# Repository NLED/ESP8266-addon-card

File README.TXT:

THERE IS NO WARRANTY FOR THE PROGRAM, TO THE EXTENT PERMITTED BY APPLICABLE LAW. 
EXCEPT WHEN OTHERWISE STATED IN WRITING THE COPYRIGHT HOLDERS AND/OR OTHER PARTIES 
PROVIDE THE PROGRAM “AS IS” WITHOUT WARRANTY OF ANY KIND, EITHER EXPRESSED OR IMPLIED,
INCLUDING, BUT NOT LIMITED TO, THE IMPLIED WARRANTIES OF MERCHANTABILITY AND FITNESS 
FOR A PARTICULAR PURPOSE. THE ENTIRE RISK AS TO THE QUALITY AND PERFORMANCE OF THE 
PROGRAM IS WITH YOU. SHOULD THE PROGRAM PROVE DEFECTIVE, YOU ASSUME THE COST OF ALL 
NECESSARY SERVICING, REPAIR OR CORRECTION.

 Original Author: Jeffrey Nygaard
 Company: Northern Lights Electronic Design, LLC
 Date: November 17, 2017
 Contact: JNygaard@NLEDshop.com
 Copyright© 2017 by Northern Lights Electronic Design, LLC. All Rights Reserved
 
;=============          www.NLEDShop.com/addoncards           ============
;=============     www.NorthernLightsElectronicDesign.com       ============

This work is licensed under a Creative Commons Attribution 4.0 International License.

Free to use for personal or commercial use, just attribute the author if releasing changes.

================================================================================================================

Ready-made devices are available for purchase, and large batch manufacturing of any device can be requested.
Please see the webpage www.NLEDShop.com/addoncards

NLED is available for custom design and manufacturing, please contact via phone or email to discuss your project.

================================================================================================================

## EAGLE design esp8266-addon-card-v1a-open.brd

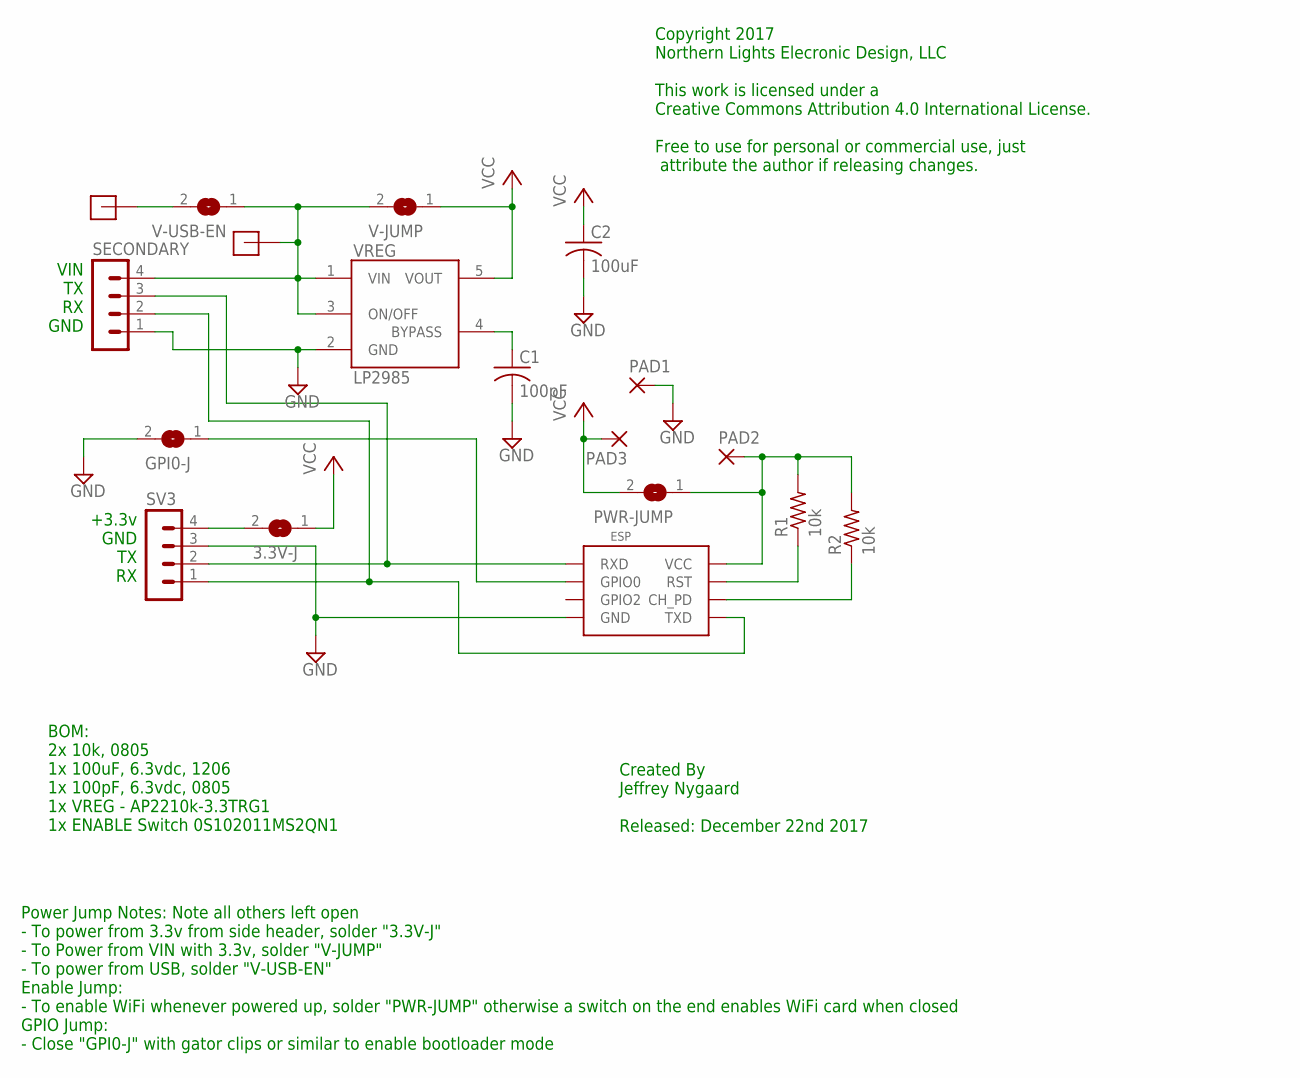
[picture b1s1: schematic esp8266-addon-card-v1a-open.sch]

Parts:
3.3V-J: SJ
C1: 100pF; C0805
C2: 100uF; C1206
ESP: ESP8266; ESP8266-2
GPI0-J: SJW
PAD1, PAD2, PAD3: SMD2; SMD1,27-2,54
PWR-JUMP: SJ
R1, R2: 10k; M0805
SECONDARY: MA04-1
SV3: MA04-1
V-JUMP: SJ
V-USB: JUMPER
V-USB-EN: SJ
VIN: JUMPER
VREG: LP2985AIM5-3.3; SOT25

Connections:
BYPASS: C1.1, VREG.4 (BYPASS)
GND: C1.2, C2.2, ESP.GND, GPI0-J.2, PAD1.1, SECONDARY.1, SV3.3, VREG.2 (GND)
unnamed: ESP.TXD, SECONDARY.2, SV3.1
unnamed: ESP.RST, R1.1
unnamed: ESP.CH_PD, R2.1
unnamed: ESP.VCC, PAD2.1, PWR-JUMP.1, R1.2, R2.2
unnamed: ESP.GPIO0, GPI0-J.1
unnamed: V-USB.2, V-USB-EN.2
unnamed: ESP.RXD, SECONDARY.3, SV3.2
unnamed: SECONDARY.4, V-JUMP.2, V-USB-EN.1, VIN.2, VREG.1 (VIN), VREG.3 (ON/OFF)
unnamed: 3.3V-J.2, SV3.4
VCC: 3.3V-J.1, C2.1, PAD3.1, PWR-JUMP.2, V-JUMP.1, VREG.5 (VOUT)

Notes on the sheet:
+3.3v GND TX RX
VIN TX RX GND
Power Jump Notes: Note all others left open - To power from 3.3v from side header, solder "3.3V-J" - To Power from VIN with 3.3v, solder "V-JUMP" - To power from USB, solder "V-USB-EN" Enable Jump: - To enable WiFi whenever powered up, solder "PWR-JUMP" otherwise a switch on the end enables WiFi ca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
Created By Jeffrey Nygaard Released: December 22nd 2017
Copyright 2017 Northern Lights Elecronic Design, LLC This work is licensed under a Creative Commons Attribution 4.0 International License. Free to use for personal or commercial use, just attribute the author if releasing changes.
BOM: 2x 10k, 0805 1x 100uF, 6.3vdc, 1206 1x 100pF, 6.3vdc, 0805 1x VREG - AP2210k-3.3TRG1 1x ENABLE Switch 0S102011MS2QN1

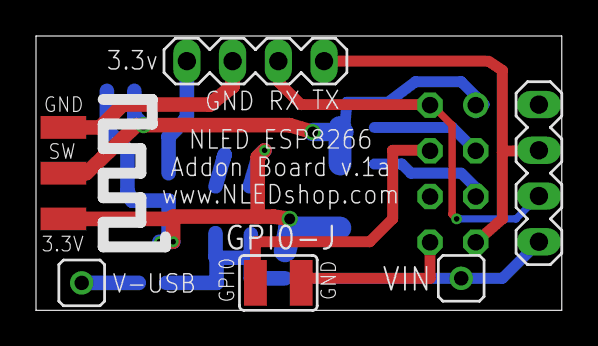
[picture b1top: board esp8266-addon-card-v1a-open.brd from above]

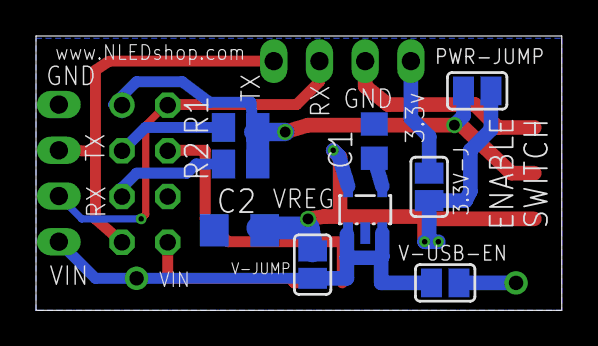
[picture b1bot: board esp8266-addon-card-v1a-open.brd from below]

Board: 2 copper layers, 29.2 x 15.2 mm, 18 parts (9 on the bottom side), 12 nets.
